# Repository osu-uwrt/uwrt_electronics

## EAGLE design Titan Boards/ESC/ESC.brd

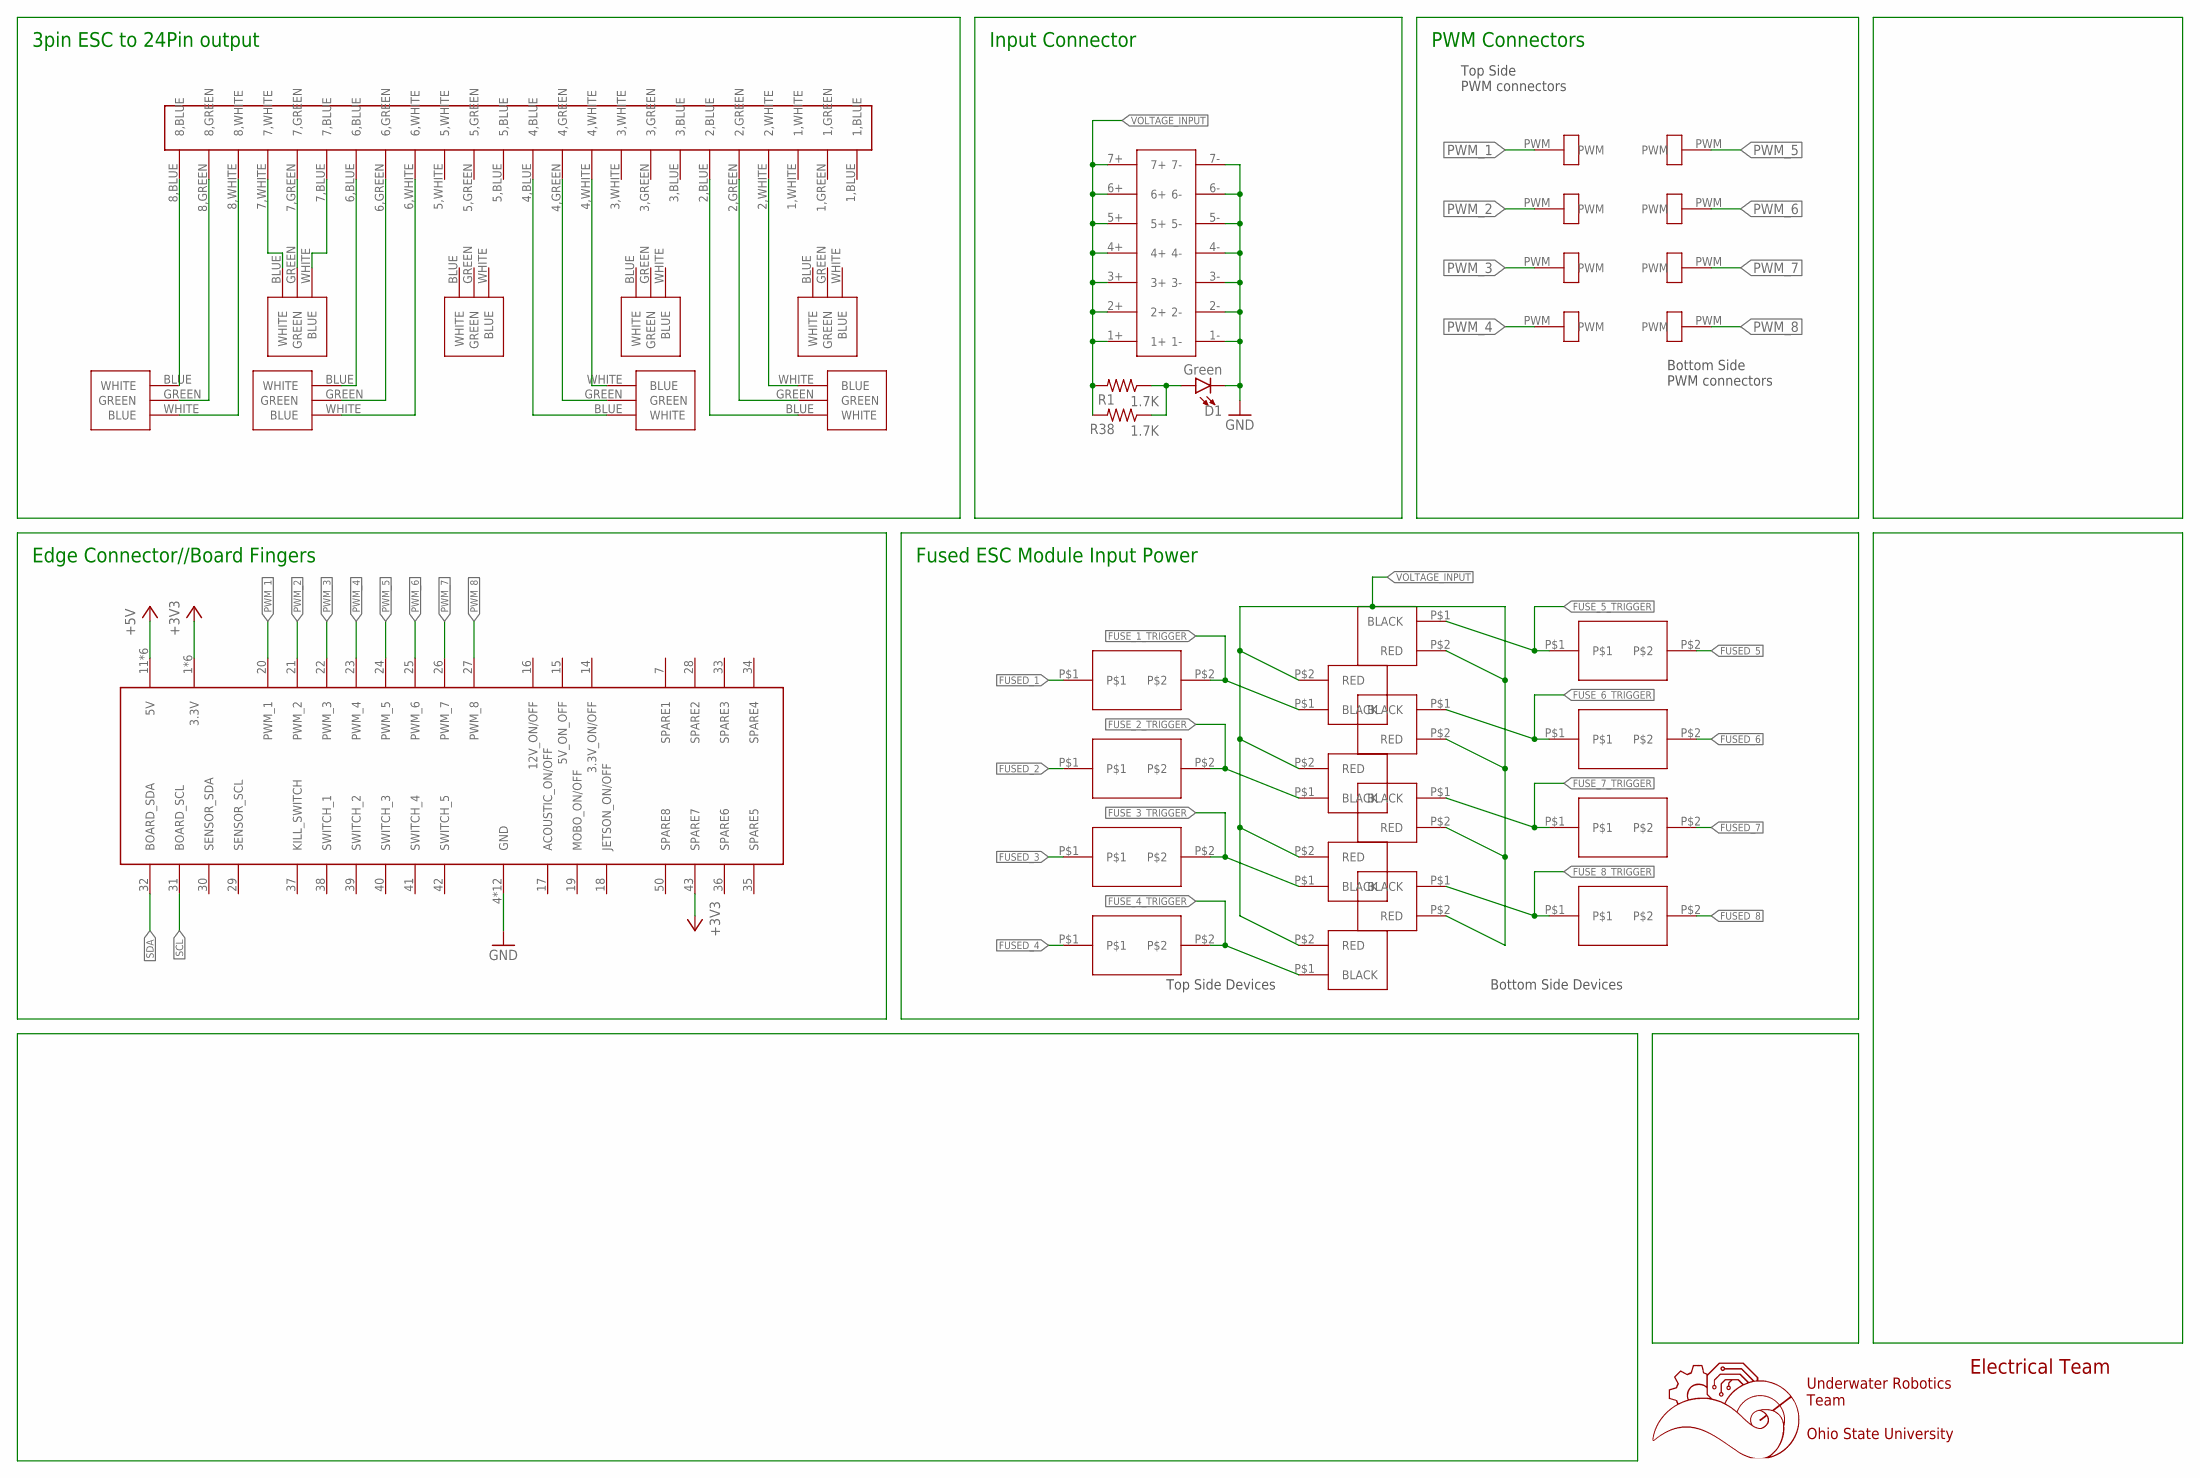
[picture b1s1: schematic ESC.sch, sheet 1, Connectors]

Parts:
2-PIN_1, 2-PIN_2, 2-PIN_3, 2-PIN_4, 2-PIN_5, 2-PIN_6, 2-PIN_7, 2-PIN_8: 1755736
3-PIN_1, 3-PIN_2, 3-PIN_3, 3-PIN_4, 3-PIN_5, 3-PIN_6, 3-PIN_7, 3-PIN_8: 1755749
24-PIN_CONNECTOR: 24PINCONVERTER
D1: Green; LED-0603
EDGE_CONNECTOR: 5530843-EDGE; 5530843-6-BOARDFINGERS
F1, F2, F3, F4, F5, F6, F7, F8: 1206FUSEHOLDER
POWER_INPUT: 14PIN_VERT
R1, R38: 1.7K; R1210
U$1, U$2, U$3, U$4, U$5, U$6, U$7, U$8: MALE1PINHEADER

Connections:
+3V3: EDGE_CONNECTOR.1 (3.3V), EDGE_CONNECTOR.2 (3.3V), EDGE_CONNECTOR.3 (3.3V), EDGE_CONNECTOR.43 (SPARE7), EDGE_CONNECTOR.54 (3.3V), EDGE_CONNECTOR.55 (3.3V), EDGE_CONNECTOR.56 (3.3V); also elsewhere on the board
+5V: EDGE_CONNECTOR.11 (5V), EDGE_CONNECTOR.12 (5V), EDGE_CONNECTOR.13 (5V), EDGE_CONNECTOR.44 (5V), EDGE_CONNECTOR.45 (5V), EDGE_CONNECTOR.46 (5V); also elsewhere on the board
FUSED_1: F1.P$1; also elsewhere on the board
FUSED_2: F2.P$1; also elsewhere on the board
FUSED_3: F3.P$1; also elsewhere on the board
FUSED_4: F4.P$1; also elsewhere on the board
FUSED_5: F5.P$2; also elsewhere on the board
FUSED_6: F6.P$2; also elsewhere on the board
FUSED_7: F7.P$2; also elsewhere on the board
FUSED_8: F8.P$2; also elsewhere on the board
FUSE_1_TRIGGER: 2-PIN_1.P$1 (BLACK), F1.P$2; also elsewhere on the board
FUSE_2_TRIGGER: 2-PIN_2.P$1 (BLACK), F2.P$2; also elsewhere on the board
FUSE_3_TRIGGER: 2-PIN_3.P$1 (BLACK), F3.P$2; also elsewhere on the board
FUSE_4_TRIGGER: 2-PIN_4.P$1 (BLACK), F4.P$2; also elsewhere on the board
FUSE_5_TRIGGER: 2-PIN_5.P$1 (BLACK), F5.P$1; also elsewhere on the board
FUSE_6_TRIGGER: 2-PIN_6.P$1 (BLACK), F6.P$1; also elsewhere on the board
FUSE_7_TRIGGER: 2-PIN_7.P$1 (BLACK), F7.P$1; also elsewhere on the board
FUSE_8_TRIGGER: 2-PIN_8.P$1 (BLACK), F8.P$1; also elsewhere on the board
GND: D1.C, EDGE_CONNECTOR.4 (GND), EDGE_CONNECTOR.5 (GND), EDGE_CONNECTOR.6 (GND), EDGE_CONNECTOR.8 (GND), EDGE_CONNECTOR.9 (GND), EDGE_CONNECTOR.10 (GND), EDGE_CONNECTOR.47 (GND), EDGE_CONNECTOR.48 (GND), EDGE_CONNECTOR.49 (GND), EDGE_CONNECTOR.51 (GND), EDGE_CONNECTOR.52 (GND), EDGE_CONNECTOR.53 (GND), POWER_INPUT.1-, POWER_INPUT.2-, POWER_INPUT.3-, POWER_INPUT.4-, POWER_INPUT.5-, POWER_INPUT.6-, POWER_INPUT.7-; also elsewhere on the board
unnamed: 3-PIN_5.BLUE (WHITE), 24-PIN_CONNECTOR.8,BLUE
unnamed: 3-PIN_5.GREEN, 24-PIN_CONNECTOR.8,GREEN
unnamed: 3-PIN_5.WHITE (BLUE), 24-PIN_CONNECTOR.8,WHITE
unnamed: 3-PIN_1.GREEN, 24-PIN_CONNECTOR.7,GREEN
unnamed: 3-PIN_6.BLUE (WHITE), 24-PIN_CONNECTOR.6,BLUE
unnamed: 3-PIN_6.GREEN, 24-PIN_CONNECTOR.6,GREEN
unnamed: 3-PIN_6.WHITE (BLUE), 24-PIN_CONNECTOR.6,WHITE
unnamed: 3-PIN_2.WHITE (BLUE), 24-PIN_CONNECTOR.5,WHITE
unnamed: 3-PIN_2.GREEN, 24-PIN_CONNECTOR.5,GREEN
unnamed: 3-PIN_2.BLUE (WHITE), 24-PIN_CONNECTOR.5,BLUE
unnamed: 3-PIN_7.BLUE (WHITE), 24-PIN_CONNECTOR.4,BLUE
unnamed: 3-PIN_7.GREEN, 24-PIN_CONNECTOR.4,GREEN
unnamed: 3-PIN_7.WHITE (BLUE), 24-PIN_CONNECTOR.4,WHITE
unnamed: 3-PIN_3.WHITE (BLUE), 24-PIN_CONNECTOR.3,WHITE
unnamed: 3-PIN_3.GREEN, 24-PIN_CONNECTOR.3,GREEN
unnamed: 3-PIN_3.BLUE (WHITE), 24-PIN_CONNECTOR.3,BLUE
unnamed: 3-PIN_4.WHITE (BLUE), 24-PIN_CONNECTOR.1,WHITE
unnamed: 3-PIN_4.BLUE (WHITE), 24-PIN_CONNECTOR.1,BLUE
unnamed: 3-PIN_4.GREEN, 24-PIN_CONNECTOR.1,GREEN
unnamed: 3-PIN_8.BLUE (WHITE), 24-PIN_CONNECTOR.2,BLUE
unnamed: 3-PIN_8.GREEN, 24-PIN_CONNECTOR.2,GREEN
unnamed: 3-PIN_8.WHITE (BLUE), 24-PIN_CONNECTOR.2,WHITE
unnamed: D1.A, R1.1, R38.1
PWM_1: EDGE_CONNECTOR.20 (PWM_1), U$1.PWM
PWM_2: EDGE_CONNECTOR.21 (PWM_2), U$2.PWM
PWM_3: EDGE_CONNECTOR.22 (PWM_3), U$3.PWM
PWM_4: EDGE_CONNECTOR.23 (PWM_4), U$4.PWM
PWM_5: EDGE_CONNECTOR.24 (PWM_5), U$5.PWM
PWM_6: EDGE_CONNECTOR.25 (PWM_6), U$6.PWM
PWM_7: EDGE_CONNECTOR.26 (PWM_7), U$7.PWM
PWM_8: EDGE_CONNECTOR.27 (PWM_8), U$8.PWM
SCL: EDGE_CONNECTOR.31 (BOARD_SCL); also elsewhere on the board
SDA: EDGE_CONNECTOR.32 (BOARD_SDA); also elsewhere on the board
VOLTAGE_INPUT: 2-PIN_1.P$2 (RED), 2-PIN_2.P$2 (RED), 2-PIN_3.P$2 (RED), 2-PIN_4.P$2 (RED), 2-PIN_5.P$2 (RED), 2-PIN_6.P$2 (RED), 2-PIN_7.P$2 (RED), 2-PIN_8.P$2 (RED), POWER_INPUT.1+, POWER_INPUT.2+, POWER_INPUT.3+, POWER_INPUT.4+, POWER_INPUT.5+, POWER_INPUT.6+, POWER_INPUT.7+, R1.2, R38.2

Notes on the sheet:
Underwater Robotics Team Ohio State University
Electrical Team
3pin ESC to 24Pin output
Input Connector
Top Side PWM connectors
Bottom Side PWM connectors
PWM Connectors
Edge Connector//Board Fingers
Fused ESC Module Input Power
Top Side Devices
Bottom Side Devices

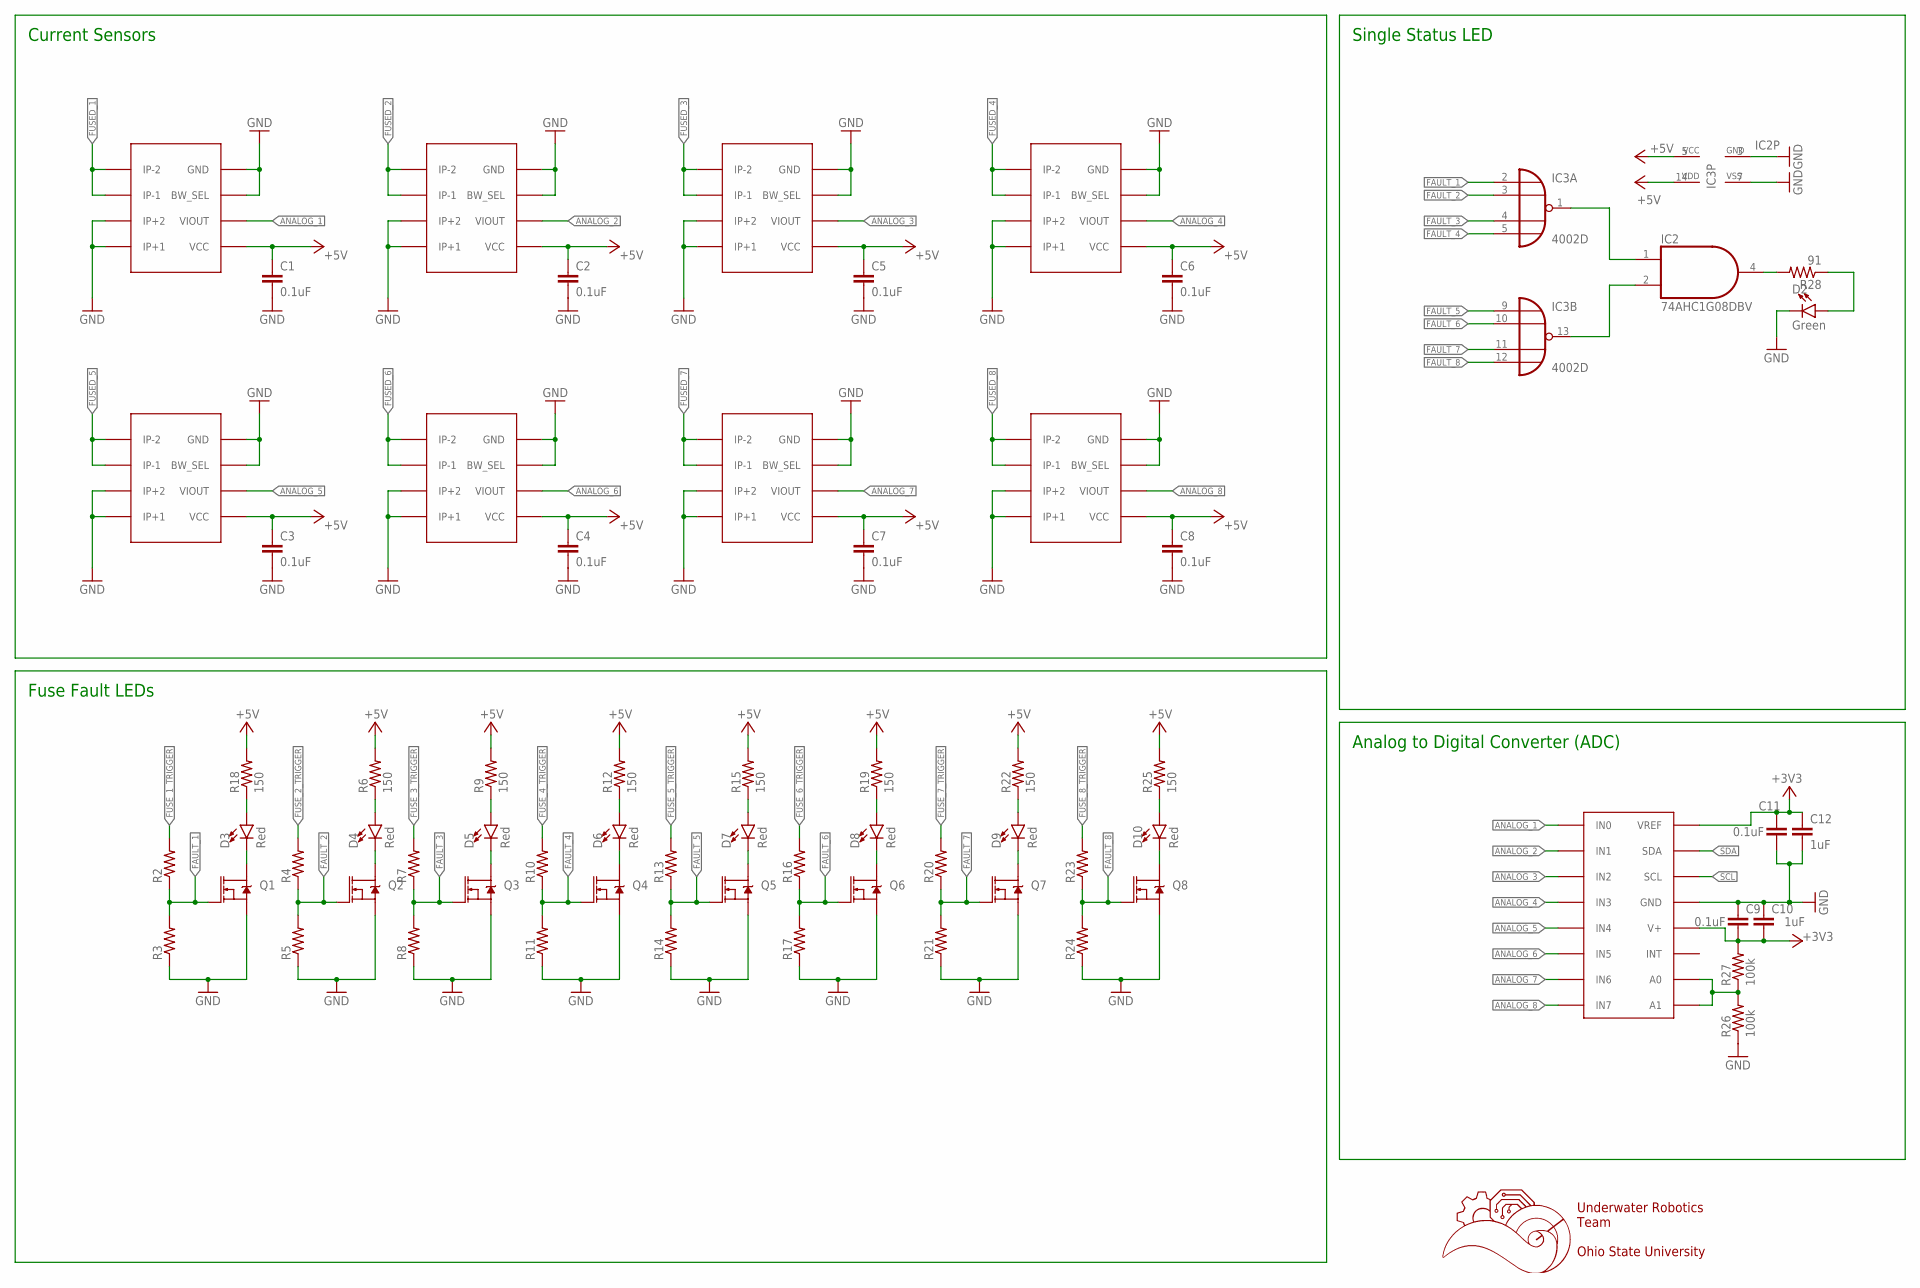
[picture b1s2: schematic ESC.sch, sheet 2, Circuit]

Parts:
C1, C2, C3, C4, C5, C6, C7, C8, C9, C11: 0.1uF; C0603
C10, C12: 1uF; C0603
CS_1, CS_2, CS_3, CS_4, CS_5, CS_6, CS_7, CS_8: ACS722; SOIC-8
D2: Green; LED-0603
D3, D4, D5, D6, D7, D8, D9, D10: Red; LED-0603
IC2: 74AHC1G08DBV; SOT23-5
IC3: 4002D; SO14
Q1, Q2, Q3, Q4, Q5, Q6, Q7, Q8: 5.8A/30V/35mΩ; SOT23-3
R2, R3, R4, R5, R7, R8, R10, R11, R13, R14, R16, R17, R20, R21, R23, R24: R-US_R0603; R0603
R6, R9, R12, R15, R18, R19, R22, R25: 150; R0603
R26, R27: 100k; R0603
R28: 91; R0603
U$11: ADC128D818; TSSOP-16

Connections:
+3V3: C9.2, C10.2, C11.1, C12.1, R27.2, U$11.V+, U$11.VREF; also elsewhere on the board
+5V: C1.1, C2.1, C3.1, C4.1, C5.1, C6.1, C7.1, C8.1, CS_1.VCC, CS_2.VCC, CS_3.VCC, CS_4.VCC, CS_5.VCC, CS_6.VCC, CS_7.VCC, CS_8.VCC, IC2.5 (VCC), IC3.14 (VDD), R6.2, R9.2, R12.2, R15.2, R18.2, R19.2, R22.2, R25.2; also elsewhere on the board
ANALOG_1: CS_1.VIOUT, U$11.IN0
ANALOG_2: CS_2.VIOUT, U$11.IN1
ANALOG_3: CS_3.VIOUT, U$11.IN2
ANALOG_4: CS_4.VIOUT, U$11.IN3
ANALOG_5: CS_5.VIOUT, U$11.IN4
ANALOG_6: CS_6.VIOUT, U$11.IN5
ANALOG_7: CS_7.VIOUT, U$11.IN6
ANALOG_8: CS_8.VIOUT, U$11.IN7
FAULT_1: IC3.2 (I0), Q1.1 (G), R2.1, R3.2
FAULT_2: IC3.3 (I1), Q2.1 (G), R4.1, R5.2
FAULT_3: IC3.4 (I2), Q3.1 (G), R7.1, R8.2
FAULT_4: IC3.5 (I3), Q4.1 (G), R10.1, R11.2
FAULT_5: IC3.9 (I0), Q5.1 (G), R13.1, R14.2
FAULT_6: IC3.10 (I1), Q6.1 (G), R16.1, R17.2
FAULT_7: IC3.11 (I2), Q7.1 (G), R20.1, R21.2
FAULT_8: IC3.12 (I3), Q8.1 (G), R23.1, R24.2
FUSED_1: CS_1.IP-1, CS_1.IP-2; also elsewhere on the board
FUSED_2: CS_2.IP-1, CS_2.IP-2; also elsewhere on the board
FUSED_3: CS_3.IP-1, CS_3.IP-2; also elsewhere on the board
FUSED_4: CS_4.IP-1, CS_4.IP-2; also elsewhere on the board
FUSED_5: CS_5.IP-1, CS_5.IP-2; also elsewhere on the board
FUSED_6: CS_6.IP-1, CS_6.IP-2; also elsewhere on the board
FUSED_7: CS_7.IP-1, CS_7.IP-2; also elsewhere on the board
FUSED_8: CS_8.IP-1, CS_8.IP-2; also elsewhere on the board
FUSE_1_TRIGGER: R2.2; also elsewhere on the board
FUSE_2_TRIGGER: R4.2; also elsewhere on the board
FUSE_3_TRIGGER: R7.2; also elsewhere on the board
FUSE_4_TRIGGER: R10.2; also elsewhere on the board
FUSE_5_TRIGGER: R13.2; also elsewhere on the board
FUSE_6_TRIGGER: R16.2; also elsewhere on the board
FUSE_7_TRIGGER: R20.2; also elsewhere on the board
FUSE_8_TRIGGER: R23.2; also elsewhere on the board
GND: C1.2, C2.2, C3.2, C4.2, C5.2, C6.2, C7.2, C8.2, C9.1, C10.1, C11.2, C12.2, CS_1.BW_SEL, CS_1.GND, CS_1.IP+1, CS_1.IP+2, CS_2.BW_SEL, CS_2.GND, CS_2.IP+1, CS_2.IP+2, CS_3.BW_SEL, CS_3.GND, CS_3.IP+1, CS_3.IP+2, CS_4.BW_SEL, CS_4.GND, CS_4.IP+1, CS_4.IP+2, CS_5.BW_SEL, CS_5.GND, CS_5.IP+1, CS_5.IP+2, CS_6.BW_SEL, CS_6.GND, CS_6.IP+1, CS_6.IP+2, CS_7.BW_SEL, CS_7.GND, CS_7.IP+1, CS_7.IP+2, CS_8.BW_SEL, CS_8.GND, CS_8.IP+1, CS_8.IP+2, D2.C, IC2.3 (GND), IC3.7 (VSS), Q1.2 (S), Q2.2 (S), Q3.2 (S), Q4.2 (S), Q5.2 (S), Q6.2 (S), Q7.2 (S), Q8.2 (S), R3.1, R5.1, R8.1, R11.1, R14.1, R17.1, R21.1, R24.1, R26.1, U$11.GND; also elsewhere on the board
unnamed: IC2.4 (O), R28.2
unnamed: D3.C, Q1.3 (D)
unnamed: D3.A, R18.1
unnamed: D4.C, Q2.3 (D)
unnamed: D4.A, R6.1
unnamed: D5.C, Q3.3 (D)
unnamed: D5.A, R9.1
unnamed: D6.C, Q4.3 (D)
unnamed: D6.A, R12.1
unnamed: D7.C, Q5.3 (D)
unnamed: D7.A, R15.1
unnamed: D8.C, Q6.3 (D)
unnamed: D8.A, R19.1
unnamed: D9.C, Q7.3 (D)
unnamed: D9.A, R22.1
unnamed: D10.C, Q8.3 (D)
unnamed: D10.A, R25.1
unnamed: D2.A, R28.1
unnamed: R26.2, R27.1, U$11.A0, U$11.A1
NOR_1_OUT: IC2.1 (I0), IC3.1 (O)
NOR_2_OUT: IC2.2 (I1), IC3.13 (O)
SCL: U$11.SCL; also elsewhere on the board
SDA: U$11.SDA; also elsewhere on the board

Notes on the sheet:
Current Sensors
Fuse Fault LEDs
Analog to Digital Converter (ADC)
Underwater Robotics Team Ohio State University
Single Status LED

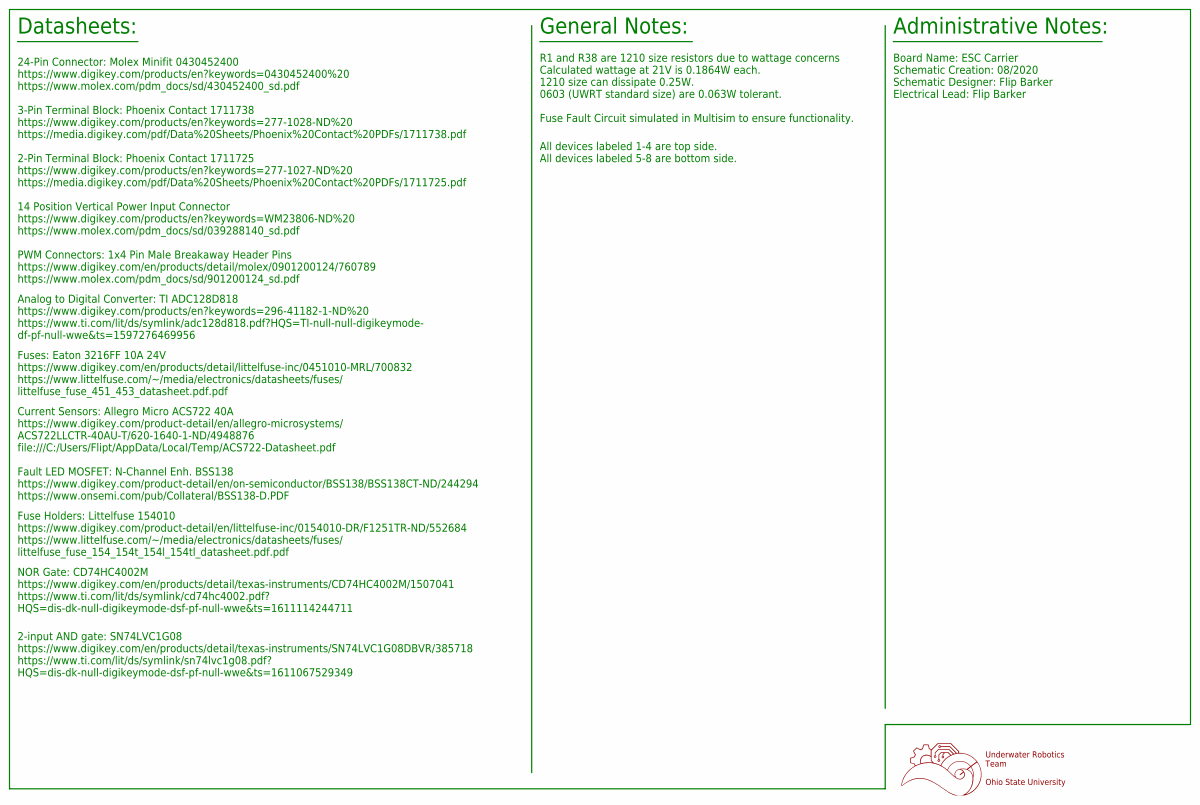
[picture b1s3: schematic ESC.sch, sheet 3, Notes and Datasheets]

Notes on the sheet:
Datasheets:
24-Pin Connector: Molex Minifit 0430452400 https://www.digikey.com/products/en?keywords=0430452400%20 https://www.molex.com/pdm_docs/sd/430452400_sd.pdf
3-Pin Terminal Block: Phoenix Contact 1711738 https://www.digikey.com/products/en?keywords=277-1028-ND%20 https://media.digikey.com/pdf/Data%20Sheets/Phoenix%20Contact%20PDFs/1711738.pdf
2-Pin Terminal Block: Phoenix Contact 1711725 https://www.digikey.com/products/en?keywords=277-1027-ND%20 https://media.digikey.com/pdf/Data%20Sheets/Phoenix%20Contact%20PDFs/1711725.pdf
General Notes:
Administrative Notes:
14 Position Vertical Power Input Connector https://www.digikey.com/products/en?keywords=WM23806-ND%20 https://www.molex.com/pdm_docs/sd/039288140_sd.pdf
PWM Connectors: 1x4 Pin Male Breakaway Header Pins https://www.digikey.com/en/products/detail/molex/0901200124/760789 https://www.molex.com/pdm_docs/sd/901200124_sd.pdf
R1 and R38 are 1210 size resistors due to wattage concerns Calculated wattage at 21V is 0.1864W each. 1210 size can dissipate 0.25W. 0603 (UWRT standard size) are 0.063W tolerant.
Fuse Fault Circuit simulated in Multisim to ensure functionality.
All devices labeled 1-4 are top side. All devices labeled 5-8 are bottom side.
Analog to Digital Converter: TI ADC128D818 https://www.digikey.com/products/en?keywords=296-41182-1-ND%20 https://www.ti.com/lit/ds/symlink/adc128d818.pdf?HQS=TI-null-null-digikeymode- df-pf-null-wwe&ts=1597276469956
Fuses: Eaton 3216FF 10A 24V https://www.digikey.com/en/products/detail/littelfuse-inc/0451010-MRL/700832 https://www.littelfuse.com/~/media/electronics/datasheets/fuses/ littelfuse_fuse_451_453_datasheet.pdf.pdf
Current Sensors: Allegro Micro ACS722 40A https://www.digikey.com/product-detail/en/allegro-microsystems/ ACS722LLCTR-40AU-T/620-1640-1-ND/4948876 file:///C:/Users/Flipt/AppData/Local/Temp/ACS722-Datasheet.pdf
Fault LED MOSFET: N-Channel Enh. BSS138 https://www.digikey.com/product-detail/en/on-semiconductor/BSS138/BSS138CT-ND/244294 https://www.onsemi.com/pub/Collateral/BSS138-D.PDF
Board Name: ESC Carrier Schematic Creation: 08/2020 Schematic Designer: Flip Barker Electrical Lead: Flip Barker
Underwater Robotics Team Ohio State University
Fuse Holders: Littelfuse 154010 https://www.digikey.com/product-detail/en/littelfuse-inc/0154010-DR/F1251TR-ND/552684 https://www.littelfuse.com/~/media/electronics/datasheets/fuses/ littelfuse_fuse_154_154t_154l_154tl_datasheet.pdf.pdf
NOR Gate: CD74HC4002M https://www.digikey.com/en/products/detail/texas-instruments/CD74HC4002M/1507041 https://www.ti.com/lit/ds/symlink/cd74hc4002.pdf? HQS=dis-dk-null-digikeymode-dsf-pf-null-wwe&ts=1611114244711
2-input AND gate: SN74LVC1G08 https://www.digikey.com/en/products/detail/texas-instruments/SN74LVC1G08DBVR/385718 https://www.ti.com/lit/ds/symlink/sn74lvc1g08.pdf? HQS=dis-dk-null-digikeymode-dsf-pf-null-wwe&ts=1611067529349

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
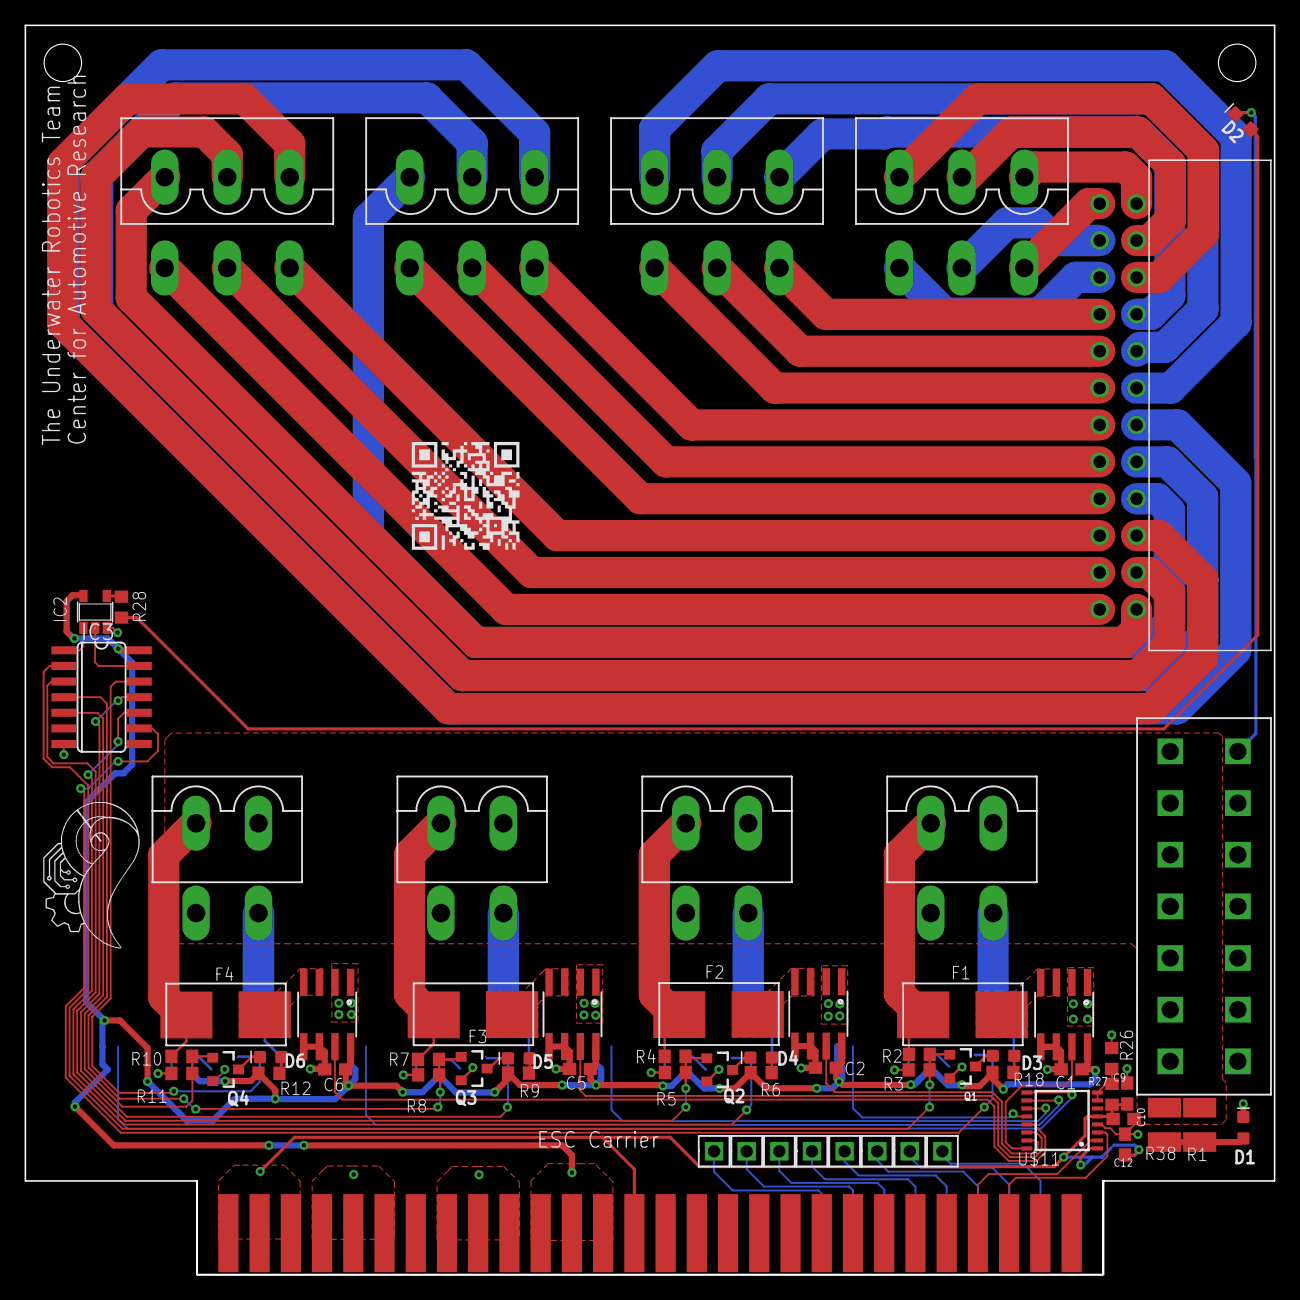
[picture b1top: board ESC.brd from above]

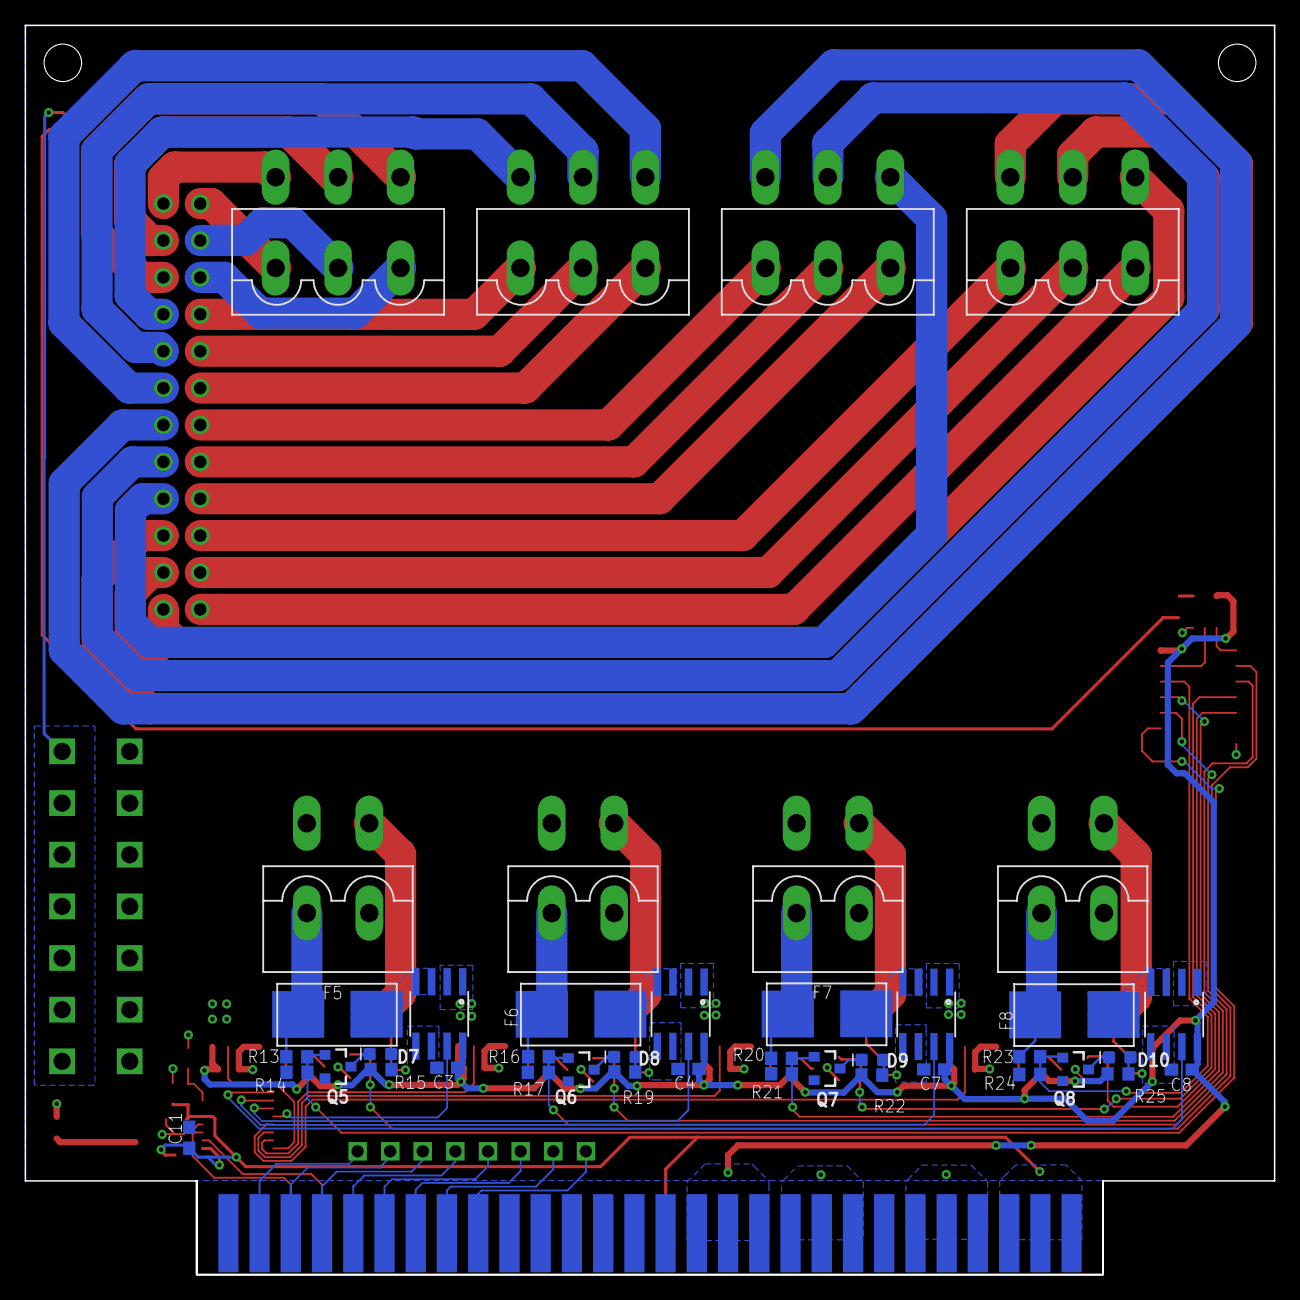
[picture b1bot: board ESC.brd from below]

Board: 2 copper layers, 101.6 x 101.6 mm, 105 parts (41 on the bottom side), 92 nets.

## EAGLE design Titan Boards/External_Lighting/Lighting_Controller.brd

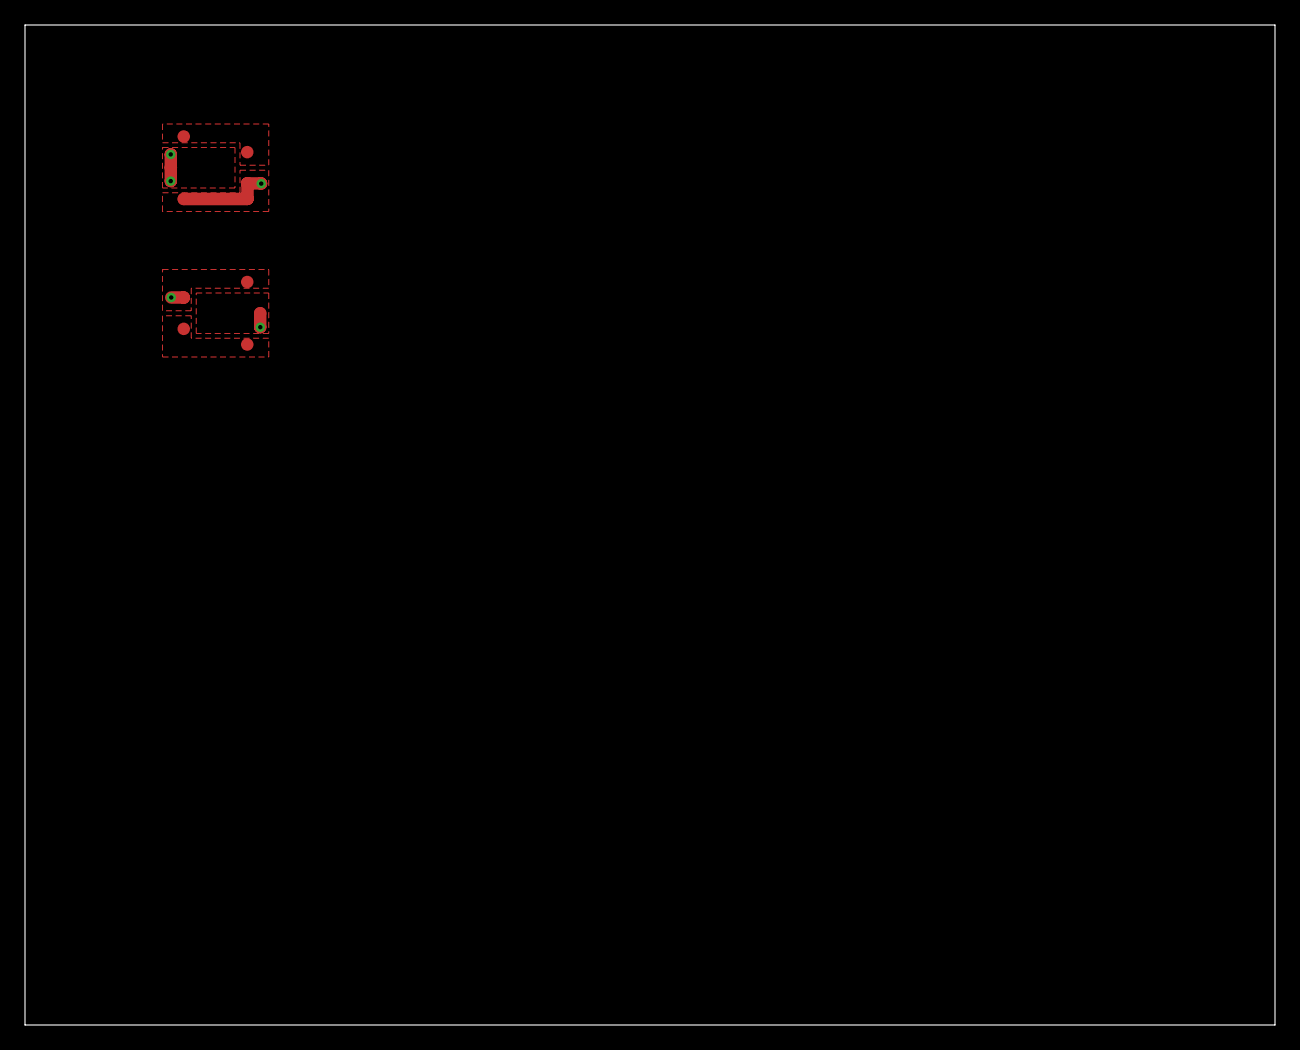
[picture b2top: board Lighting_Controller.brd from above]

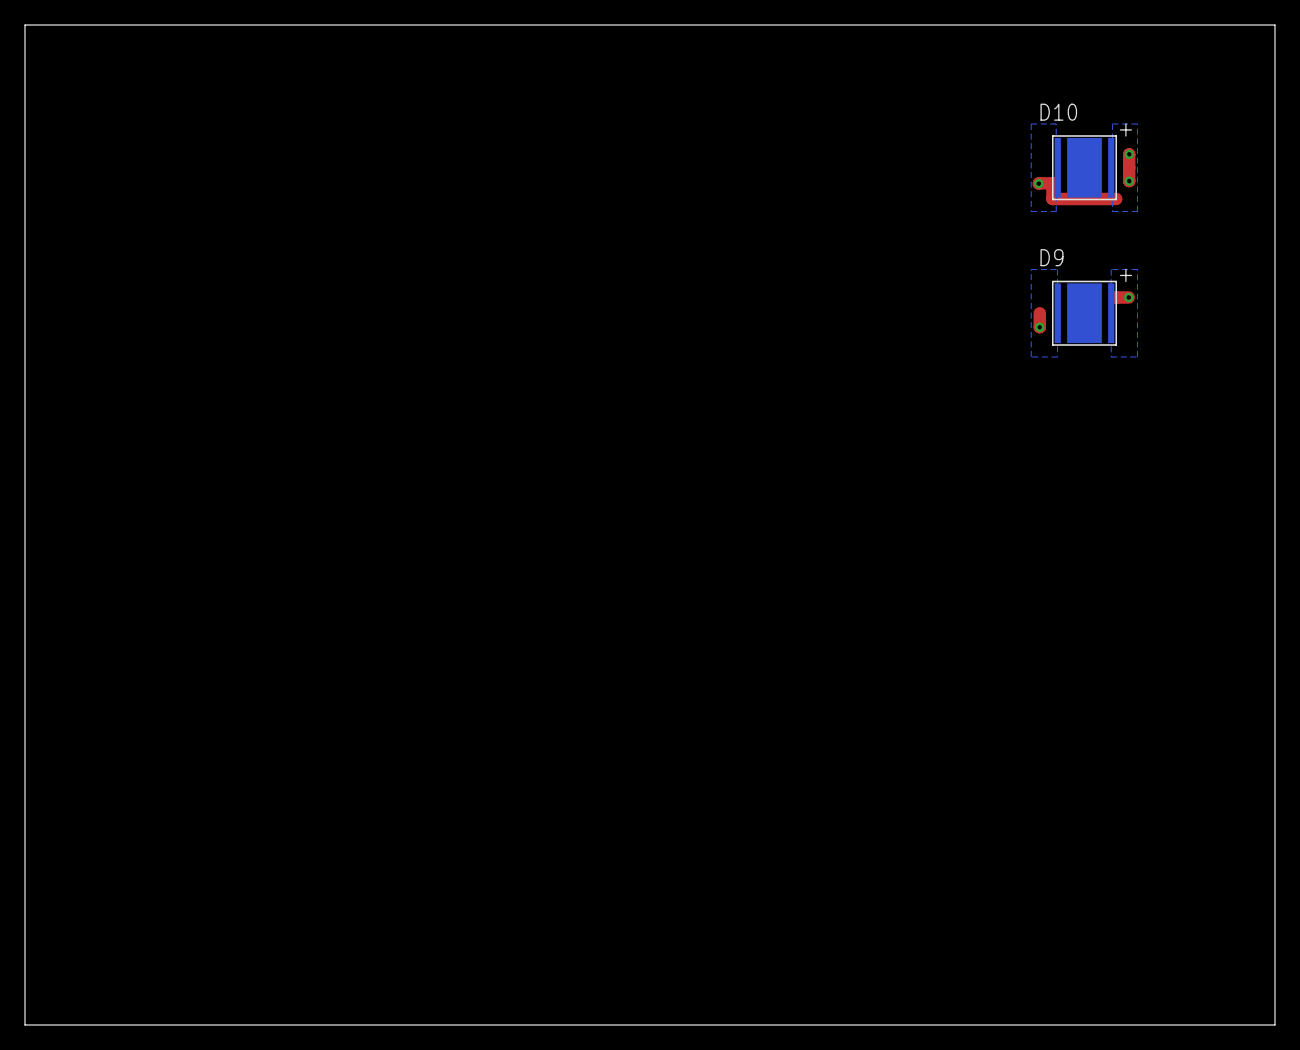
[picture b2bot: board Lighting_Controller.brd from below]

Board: 2 copper layers, 100.0 x 80.0 mm, 6 parts (2 on the bottom side), 4 nets.

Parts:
D9, D10: XLAMP_XM-L2
J1, J2: SOLDER2PAD
J3, J4: SOLDER3PAD

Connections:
12V: D9.1, J1.P$2, J2.P$1, J3.P$3, J4.P$1
GND: D10.2, J1.P$1, J2.P$2, J3.P$1, J4.P$3
unnamed: D10.1, J4.P$2
unnamed: D9.2, J3.P$2

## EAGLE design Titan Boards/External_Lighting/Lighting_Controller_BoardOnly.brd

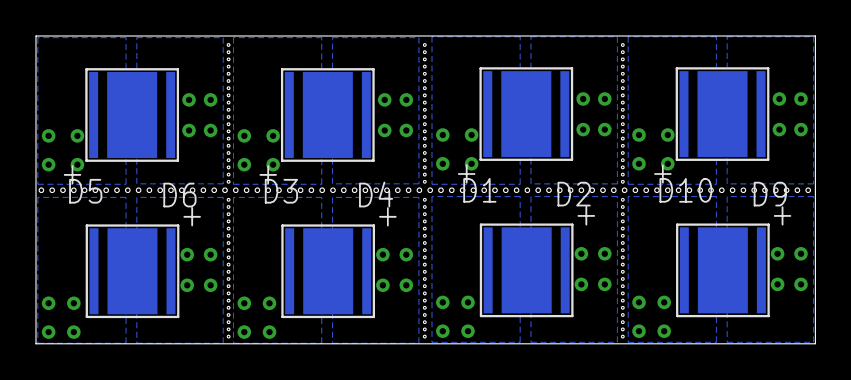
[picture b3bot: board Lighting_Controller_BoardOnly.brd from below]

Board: 2 copper layers, 43.3 x 17.1 mm, 8 parts (8 on the bottom side), 4 nets, no tracks yet.

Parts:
D1, D2, D3, D4, D5, D6, D9, D10: XLAMP_XM-L2

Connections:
unnamed: D1.1, D2.2
unnamed: D3.1, D4.2
unnamed: D5.1, D6.2
unnamed: D9.2, D10.1

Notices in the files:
parts and their libraries:
SparkFun-LED: Licensing: Creative Commons ShareAlike 4.0 International - https://creativecommons.org/licenses/by-sa/4.0
